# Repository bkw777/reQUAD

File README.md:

# reQUAD

## About
This is a derivative of [QUAD](http://bitchin100.com/wiki/index.php?title=QUAD) by Steve Adolph.

## Differences from the original
Removed the resistor-cap power-on-reset circuit and resettable flip-flop for a simple flip-flop.  
Added battery and battery-change cap.  
Added pulldown on the sram CE2.

## To Build it
PCB [PCBWAY](https://www.pcbway.com/project/shareproject/reQUAD_RAM_Expansion_for_TRS_80_Model_100_8690cd19.html)  
BOM [DigiKey](https://www.digikey.com/short/z47bn0mw)

Build notes,  
The pin 1 mark on DA1, BAV756S, is tiny and faint, but there is one, you just need a lot of magnification and light. The markings look like `.A7t` and the . is at pin 1. The pinout is not symmetric, and so the part must be installed in the correct orientation.

## To Use it

The device disables and replaces the machine's original internal 32k RAM, so copy any files off of the computer before installing the reQUAD. You won't be able to access the internal ram except by removing the reQUAD.

The first time the device is powered up, it will be in a random bank number.

The first thing you should do after install is "blindly" switch to each bank,  
and do a cold-reset in each bank to wipe all banks of any random data.  
(only cold-reset, not power-cycle. If you power-cycle, the reQUAD may switch to a random bank again.)

In BASIC type `OUT 128,3` \[Enter\], then CTRL+BREAK+RESET.  
In BASIC type `OUT 128,2` \[Enter\], then CTRL+BREAK+RESET.  
In BASIC type `OUT 128,1` \[Enter\], then CTRL+BREAK+RESET.  
In BASIC type `OUT 128,0` \[Enter\], then CTRL+BREAK+RESET.  

Now all 4 banks have been wiped clean of any random data, and you are sitting in bank 1.  
From now on, don't do CTRL+BREAK+RESET any more, just RESET (unless you actually want to wipe a bank).  

Now there are 3 main options for using the banks from no on.  
Manual control,  
BANK.BA,  
0QUAD

### Manual Control

To switch banks manually without 0QUAD or BANK.BA:  
In BASIC, type `OUT 128,n`, where n is the desired bank number from 0 to 3,  
then immediately press RESET on the back of the machine.

`OUT 128,0` switches to bank 1  
`OUT 128,1` switches to bank 2  
`OUT 128,2` switches to bank 3  
`OUT 128,3` switches to bank 4  

The cpu has no knowledge that it's entire ram universe has been replaced and all it's current register contents and pointers and such are invalid, so the main rom must be restarted IMMEDIATELY after the OUT command.

So after the OUT command, ignore the screen and press the RESET button on the back of the machine.

Pressing RESET is only needed when switching manually this way instead of using BANK.BA or 0QUAD.  
BANK.BA and 0QUAD both induce a reset themselves.

### BANK.BA
The next-simplest option for controlling the reQUAD is to copy this 4-line BASIC program into each bank,  
and save it with a name matching the current bank it's in.

First, ensure you are in bank 1:  
In BASIC, type `OUT128,0` \[Enter\], then press RESET.

Then in BASIC type-in this program:
```
1 INPUT"Bank(1-4)";X:IFX<1ORX>4THEN 1
2 A#=0:B=VARPTR(A#):POKEB,249
3 POKEB+1,195:POKEB+2,241:POKEB+3,118
4 CALLB,X-1,30481
```

Then `SAVE "BANK1"`

Now you know you are in bank1 because it says BANK1.BA in the main menu,  
and you can BANK1.BA to switch to any other bank.

Repeat for all 4 banks  
run BANK1.BA, answer "2", you are now in a new empty bank2, type-in the program again, `SAVE "BANK2"`  
run BANK2.BA, answer "3", type-in, `SAVE "BANK3"`  
run BANK3.BA, answer "4", type-in, `SAVE "BANK4"`  

### 0QUAD

Install [0QUAD](APP/)

Refer to the docs for the original [QUAD](http://bitchin100.com/wiki/index.php?title=QUAD)

### Example Installing 0QUAD using dl2 and teeny
(this will wipe all data)

QUAD.BA must be copied as a binary via TPDD, it can't be copied in ascii format using ordinary text transfer with TELCOM.  

This example will use dl2 on the pc to bootstrap install TEENY on the 100, and then use TEENY and dl2 to copy QUAD.BA to the 100.
You can use any other TPDD emulator instead of dl2, like LaddieAlpha or a Backpack, and you can use any TPDD client instead of TEENY, like TS-DOS or DSKMGR.

On the pc, install [dl2](https://github.com/bkw777/dl2/)

On the 100, in BASIC: `OUT 128,0`  
Then do a cold reset: CTRL+BREAK+RESET

On the pc:
```
$ cd APP
$ dl -v -b TEENY.100 && dl -v -u
```

On the 100, in BASIC: `RUN "COM:98N1ENN"`  
Press ENTER at the end of the TEENY install to accept the default install location.  
`CLEAR 0,62213`  
Press F8 to exit to the main menu and run TEENY.CO  
Use TEENY to copy QUAD.BA from the pc  
```
> L QUAD  .BA
> Q
```

On the pc: Ctrl+C to exit dl2

On the 100: Run QUAD.BA  
Answer "1" to the "Which bank are you in?" question.  

0QUAD is now installed in bank 1, but is invisible.

Type `0QUAD` \[Enter\] at the main menu (not in BASIC) to run 0QUAD

Now the top-right corner will show "#1" to show that you are currently in bank 1.  
Press F1 to pull up the bank-switch menu, then press F2 to switch to bank 2.

You are now in bank 2 which is a new empty bank.  
0QUAD is not installed in this bank yet.

Install 0QUAD in bank 2 by repeating everything after the OUT command above, including the cold reset.  
Answer "2" at the "Which bank?" question.  
Repeat again for banks 3 and 4.

Once 0QUAD is installed in all banks, you can use it to switch from any bank to any other bank, and you don't need to press the RESET button after each switch when using 0QUAD to switch.

## Thanks
Thanks to Steve Adolph for sharing his original design and allowing this derivative.

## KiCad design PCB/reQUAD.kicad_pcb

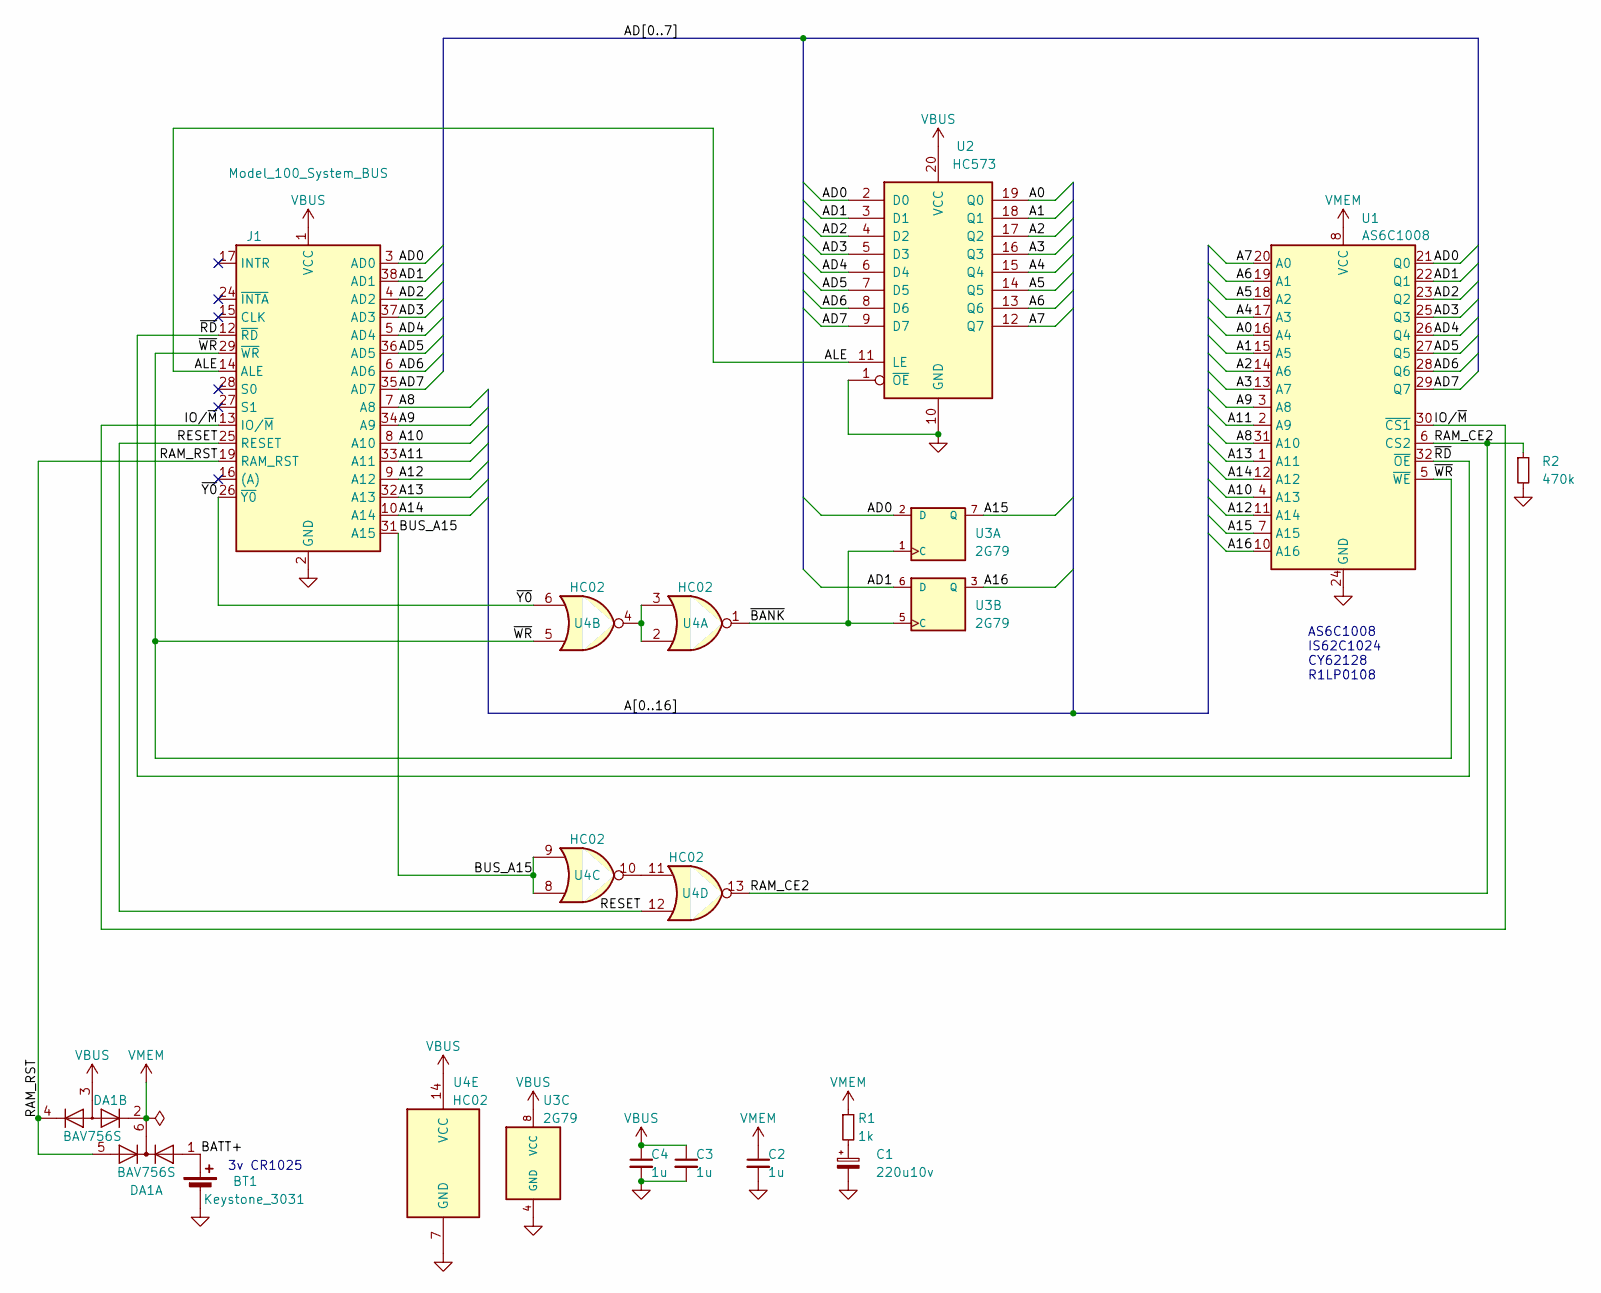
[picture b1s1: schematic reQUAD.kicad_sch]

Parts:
BT1: Keystone_3031; MPN Keystone 3031
C1: 220u10v; CP_6032; MPN TAJC227K010RNJ
C2, C3, C4: 1u; C_0805; MPN CL21B105KAFNNNE
DA1: BAV756S; SOT-363; MPN BAV756S,115
J1: Model_100_System_BUS; DIP-40_PCB; MPN 920-0172-01
R1: 1k; R_0805; MPN RK73B2ATTD102J
R2: 470k; R_0805; MPN RC0805FR-07470KL
U1: AS6C1008; TSOP32-dual; MPN AS6C1008-55STIN
U2: HC573; TSSOP-20_4.4x6.5mm_P0.65mm; MPN 74HC573PW,118
U3: 2G79; VSSOP-8_2.3x2mm_P0.5mm; MPN SN74LVC2G79DCUR
U4: HC02; TSSOP-14_4.4x5mm_P0.65mm; MPN 74HC02PW,118

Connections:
/A0: U1.16 (A4), U2.19 (Q0)
/A1: U1.15 (A5), U2.18 (Q1)
/A2: U1.14 (A6), U2.17 (Q2)
/A3: U1.13 (A7), U2.16 (Q3)
/A4: U1.17 (A3), U2.15 (Q4)
/A5: U1.18 (A2), U2.14 (Q5)
/A6: U1.19 (A1), U2.13 (Q6)
/A7: U1.20 (A0), U2.12 (Q7)
/A8: J1.7 (A8), U1.31 (A10)
/A9: J1.34 (A9), U1.3 (A8)
/A10: J1.8 (A10), U1.4 (A13)
/A11: J1.33 (A11), U1.2 (A9)
/A12: J1.9 (A12), U1.11 (A14)
/A13: J1.32 (A13), U1.1 (A11)
/A14: J1.10 (A14), U1.12 (A12)
/A15: U1.7 (A15), U3.7 (Q)
/A16: U1.10 (A16), U3.3 (Q)
/AD0: J1.3 (AD0), U1.21 (Q0), U2.2 (D0), U3.2 (D)
/AD1: J1.38 (AD1), U1.22 (Q1), U2.3 (D1), U3.6 (D)
/AD2: J1.4 (AD2), U1.23 (Q2), U2.4 (D2)
/AD3: J1.37 (AD3), U1.25 (Q3), U2.5 (D3)
/AD4: J1.5 (AD4), U1.26 (Q4), U2.6 (D4)
/AD5: J1.36 (AD5), U1.27 (Q5), U2.7 (D5)
/AD6: J1.6 (AD6), U1.28 (Q6), U2.8 (D6)
/AD7: J1.35 (AD7), U1.29 (Q7), U2.9 (D7)
/ALE: J1.14 (ALE), U2.11 (LE)
/BATT+: BT1.1 (+), DA1.1 (A1)
/BUS_A15: J1.31 (A15), U4.8, U4.9
/IO/~M: J1.13 (IO/~M), U1.30 (~CS1)
/RAM_CE2: R2.1, U1.6 (CS2), U4.13
/RAM_RST: DA1.4 (K3), DA1.5 (A4), J1.19 (RAM_RST)
/RESET: J1.25 (RESET), U4.12
/~BANK: U3.1 (C), U3.5 (C), U4.1
/~RD: J1.12 (~RD), U1.32 (~OE)
/~WR: J1.29 (~WR), U1.5 (~WE), U4.5
/~Y0: J1.26 (~Y0), U4.6
GND: BT1.2 (-), C1.2, C2.2, C3.2, C4.2, J1.2 (GND), J1.11 (GND), J1.18 (GND), J1.23 (GND), J1.30 (GND), J1.39 (GND), R2.2, U1.24 (GND), U2.1 (~OE), U2.10 (GND), U3.4 (GND), U4.7 (GND)
unnamed: C1.1, R1.2
unnamed: U4.2, U4.3, U4.4
unnamed: U4.10, U4.11
VBUS: C3.1, C4.1, DA1.3 (CA), J1.1 (VCC), J1.40 (VCC), U2.20 (VCC), U3.8 (VCC), U4.14 (VCC)
VMEM: C2.1, DA1.2 (K2), DA1.6 (CK), R1.1, U1.8 (VCC)

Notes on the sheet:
3v CR1025
AS6C1008 IS62C1024 CY62128 R1LP0108

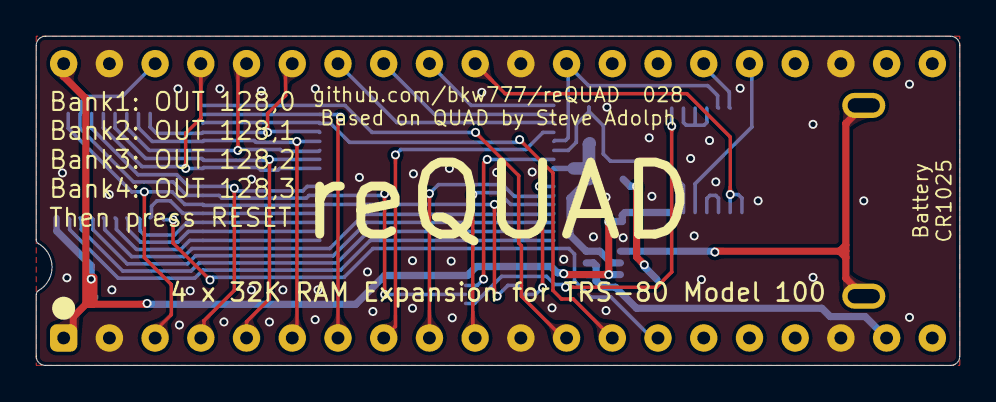
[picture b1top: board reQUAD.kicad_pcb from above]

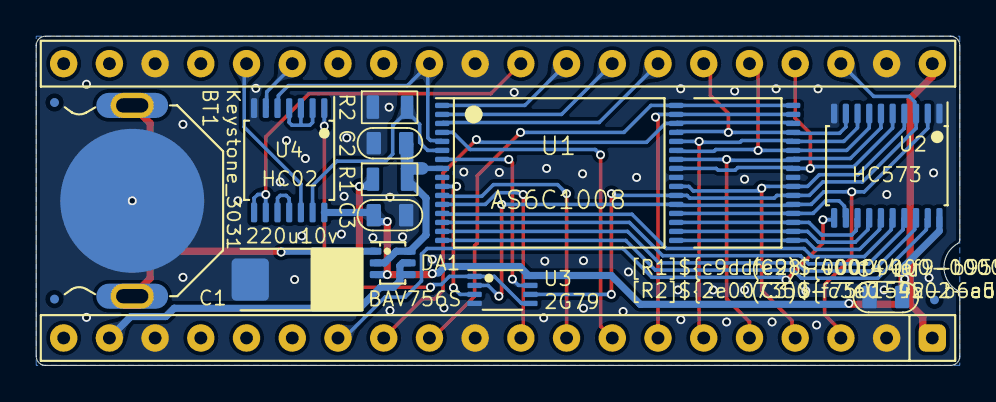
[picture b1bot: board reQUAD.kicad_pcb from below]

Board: 2 copper layers, 51.3 x 18.3 mm, 16 parts (16 on the bottom side), 42 nets.

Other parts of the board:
F1, F2, F3: Fiducial_0.5_1.0

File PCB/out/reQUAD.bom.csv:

"Reference","Value","Datasheet","Footprint","Qty","DNP","MPN","Description"
"BT1","Keystone_3031","datasheet/Keystone_3031.pdf","000_LOCAL:Keystone_3031","1","","Keystone 3031","Battery Retainer Coin, 10.0mm 1 Cell PC Pin"
"C1","220u10v","datasheets/TAJ.odf","000_LOCAL:CP_6032","1","","TAJC227K010RNJ","CAP TANT 220UF 10% 10V 2312"
"C2,C3,C4","1u","datasheets/CL21B105KAFNNNE.pdf","000_LOCAL:C_0805","3","","CL21B105KAFNNNE","CAP CER 1UF 25V X7R 0805"
"DA1","BAV756S","datasheets/BAV756S.pdf","000_LOCAL:SOT-363","1","","BAV756S,115","DIODE ARRAY GP 90V 250MA 6TSSOP"
"J1","Model_100_System_BUS","datasheets/TRS-80_Model_100_User_Guide.pdf","000_LOCAL:DIP-40_PCB","1","","920-0172-01","CONN HEADER VERT 40P 2.54MM"
"R1","1k","datasheets/RK73.pdf","000_LOCAL:R_0805","1","","RK73B2ATTD102J","RES 1K OHM 5% 1/4W 0805"
"R2","470k","datasheets/PYu-RC_Group_51_RoHS_L_12.pdf","000_LOCAL:R_0805","1","","RC0805FR-07470KL","RES 470K OHM 1% 1/8W 0805"
"U1","AS6C1008","datasheets/AS6C1008.pdf","000_LOCAL:TSOP32-dual","1","","AS6C1008-55STIN","IC SRAM 1Mx8 PARALLEL 5V 32STSOP"
"U2","HC573","datasheets/HC573.pdf","000_LOCAL:TSSOP-20_4.4x6.5mm_P0.65mm","1","","74HC573PW,118","IC D-TYPE TRANSP SGL 8:8 20TSSOP"
"U3","2G79","datasheets/2G79.pdf","000_LOCAL:VSSOP-8_2.3x2mm_P0.5mm","1","","SN74LVC2G79DCUR","Flip Flop 2 Element D-Type 1 Bit Positive Edge 8-VFSOP (0.091"", 2.30mm Width)"
"U4","HC02","datasheets/HC02.pdf","000_LOCAL:TSSOP-14_4.4x5mm_P0.65mm","1","","74HC02PW,118","IC GATE NOR 4CH 2-INP 14TSSOP"

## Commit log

2022-08-22 initial
2022-08-22 increase few minor clearances
2022-08-22 silkscreen
2022-08-22 oshpark
2022-08-23 v002
2022-08-23 v003
2022-08-23 v004
2022-08-23 v005
2022-08-23 v006
2022-08-23 v007
2022-08-23 v010
2022-08-24 Try Steve's new idea: Pull (A)* low instead of pulling RAMRST high
2022-08-29 pcb routing vcc vmem A0-A3
2022-08-29 vias on vcc & vmem
2022-08-29 vcc routing
2022-08-30 renders and minor pcb layout adjustments
2022-08-30 dip pins footprint & board outline
2022-08-30 outline, fiducials
2022-09-07 smaller file size 3d model for pins
2022-10-06 only need the flipflops on vmem?
2022-10-06 flipflop datasheet
2022-10-13 docs
2023-04-14 add vcc cap
2023-04-14 pics
2023-09-01 standard pins, add 47u on vmem
2023-09-01 readme
2023-09-04 renders & readme
2023-09-24 volotile latches, battery
2023-09-25 datasheets
2023-09-26 tiny pcb layout nudges
2023-09-26 make v020 main even though not tested yet
2023-10-02 add series resistor on tantalum
2023-10-03 routing R2
2023-10-03 R1 more common value
2023-10-17 docs, v022 is tested working
2023-10-18 add fiducials
2023-11-05 batt footprint, vbus & gnd routing near pin 1
2023-11-22 battery footprint
2023-12-18 sch tidy
2024-03-07 kicad 8
2024-08-01 img links in readme
2024-11-21 improve hand-solderability of TSSOP parts
2024-11-21 TSSOP footprints, silkscreen, MPN & bom export from sch, centroid export
2024-11-21 TSOP32 footprint, arrange R1 R2 C2 C3 for easier hand soldering
2024-11-23 028 - tsop32 footprint
2025-01-18 make BANK.DO fit in 40 columns
2025-03-01 correct MPN for VSSOP-8 package 2G79
